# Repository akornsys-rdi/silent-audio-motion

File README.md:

# Silent audio motion

Silent audio motion, the system behind «Ver no es hablar» artwork

## Description

The device generates the movement of a magnet according to an input audio signal. For this purpose the device generates a PWM signal with polarity (positive and negative half cycle) to excite an electromagnet. This signal is proportional to an analog input signal (audio source). It has two symmetrical channels and it responds to different frequencies, signal levels and waveforms.

This repository includes all the necessary files of this project: The 3D files to be printed, the control board of the device and its firmware.

### Technical features

- Supply voltage: 12VDC
- Frequency range: 1KHz-0.1Hz (firmware capability)
- Input voltage: up to 3Vpp
- Input impedance: 20kΩ

### Status LED

The device includes an LED to show the state it is in, these states are:

- Permanent LED indicates that there is no signal on either channel, the output driver is off.
- Slow blinking LED (~8Hz) indicates clipping on output, input level needs to be lowered or ADJ trimmer needs to be adjusted if not calibrated.
- Fast flashing LED (~30Hz) indicates input level too high, input level needs to be lowered, input stage may be damaged.
- LED off in normal operation.

The status LED may take up to one second to respond to changes in the input.

## Testing the device

### Output driver test

Load the `test_outputs` program. It should generate signals on both output channels. The test firmware can generate different output patterns.
The test is successful when the solenoid connected to each channel moves at the frequency set in code, with the selected waveform.

### Input stage test

Load the 'test_inputs' program. The cursor of the trimmers must not be at the ends. This program must show per port the three inputs of each channel (use serial plotter). Connect an audio source with a signal below 10Hz to both channels.

The test is successful when:

- The values of the first and fourth signals should be the values of the inputs of the left and right audio channels respectively.
- The values of the second and fifth signals should be the values of the ADJ trimmers, and should be different from the ends.
- The values of the third and sixth signals are a comparison of the negative half-cycle with the TRG trimmers, and should show a square signal centered on the peaks of the audio inputs. If this square signal does not appear, move the TRG trimmers until it does.

One of the input signal half-cycles may be slightly smaller than the other.

## Calibrating the device

Set the 3Hz and 3Vpp sine wave signal to channel L, with the program 'test_inputs' loaded.

Adjust the ADJ trimmer immediately above the peak of the input signal, and below the STANDBY_THRESHOLD threshold (default 900). A good value is 817. Turning it counterclockwise increases the value, and turning it clockwise decreases it.

Change the frequency to 0.5Hz. Adjust the ADJ trimmer until it is as close to zero as possible. It should be shown only during negative half-cycles. Values too low show square signals during both half-cycles. Values too high are far from zero on negative half-cycles.
A good adjustment is to lower it until it is below zero and to go up until the trigger disappears in the positive semicircle, then add a quarter turn more. Turning clockwise lowers the value, turning counterclockwise raises it.

Repeat the process with the R channel.

Enter signal on both channels, the setting signals must overlap.

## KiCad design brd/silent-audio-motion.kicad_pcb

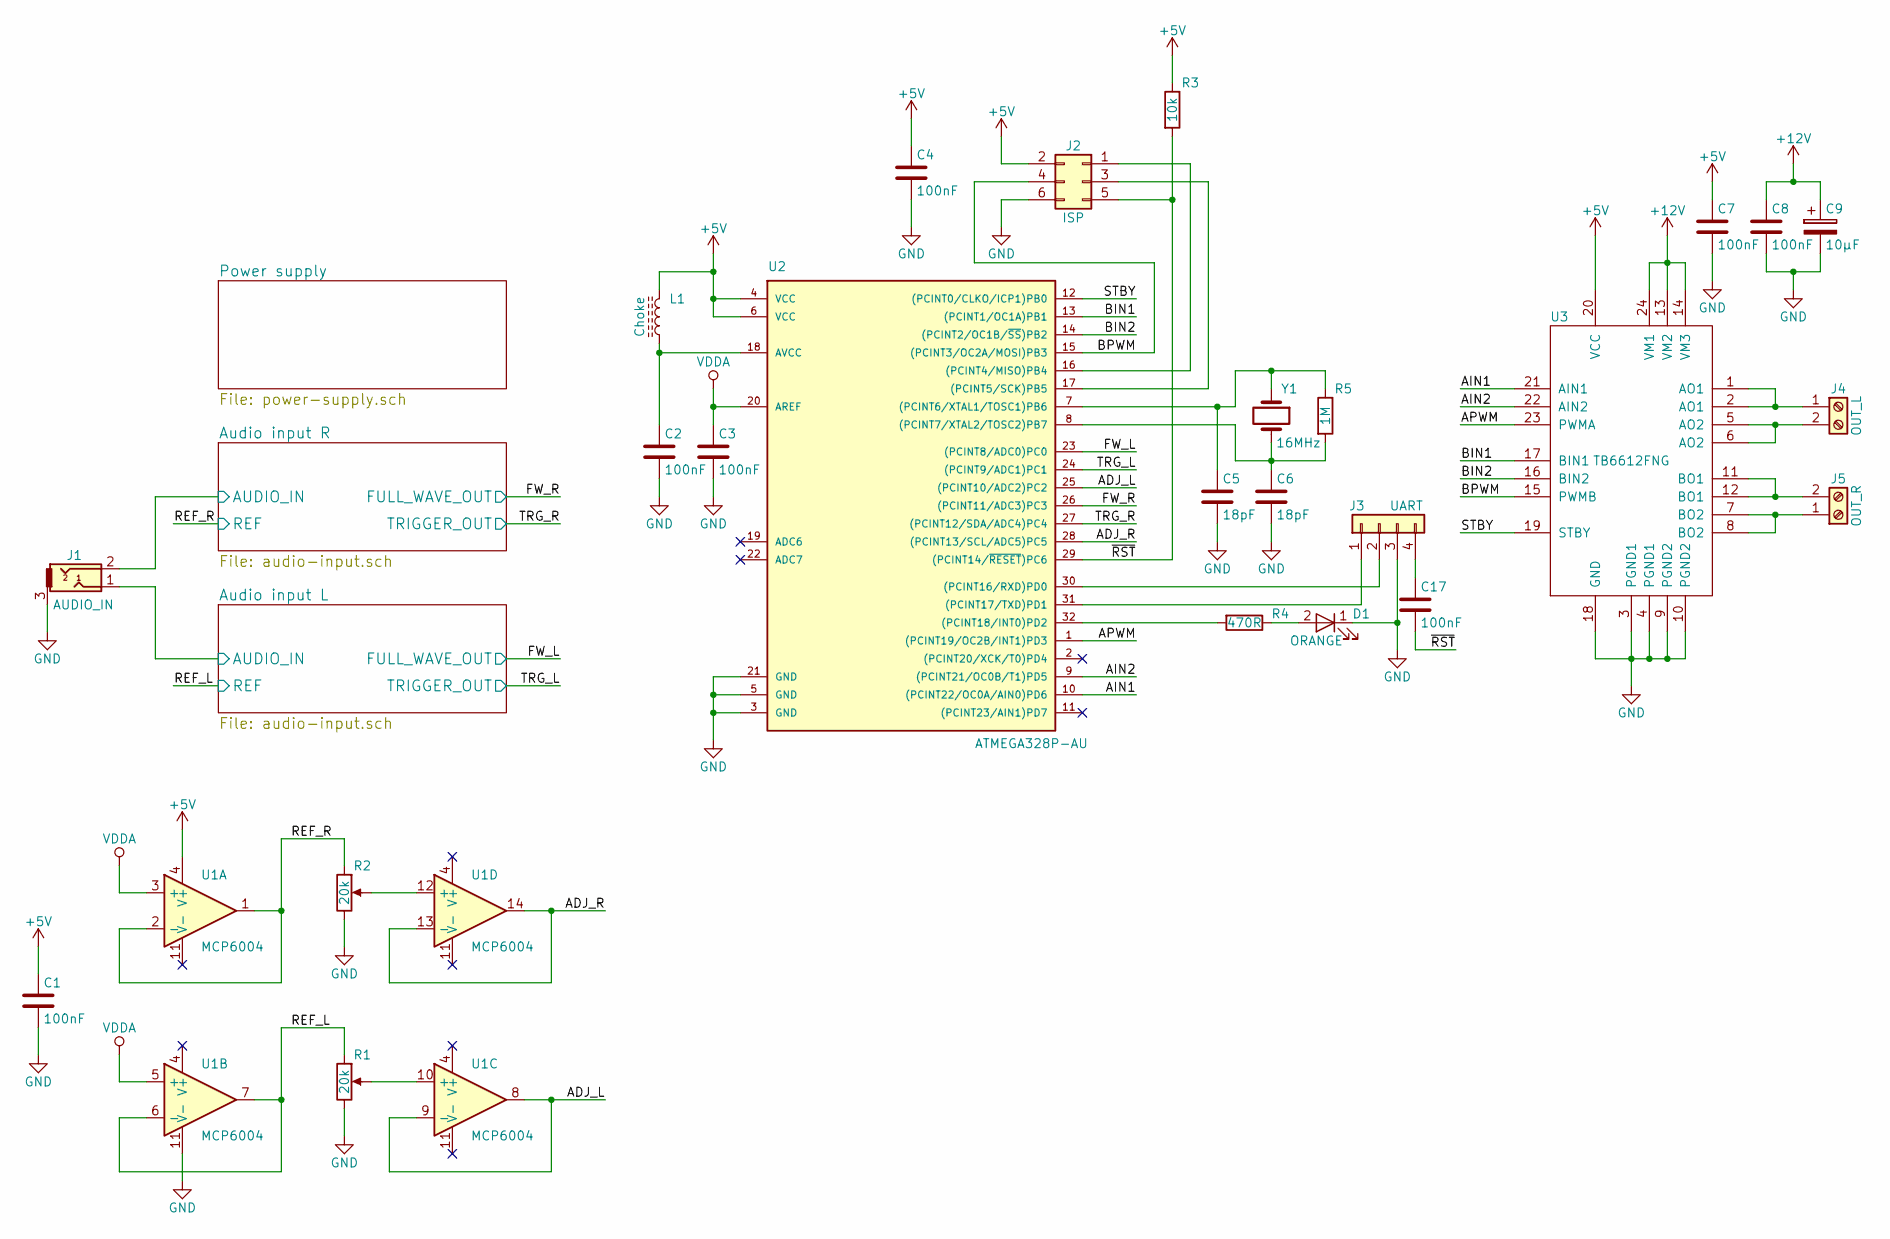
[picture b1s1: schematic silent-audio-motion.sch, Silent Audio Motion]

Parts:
C1, C2, C3, C4, C7, C8, C17: 100nF; C_0805; Manufacturer Part Number C0805C104J5RACTU
C5, C6: 18pF; C_0805; Manufacturer Part Number C0805C180J5GAC
C9: 10µF; CP_Elec_4x5.3; Manufacturer Part Number UWJ1C100MCL1GB
D1: ORANGE; LED_0805; Manufacturer Part Number LO R976-PS-1
J1: AUDIO_IN; STX-3200-3; Manufacturer Part Number STX-3200-3NB
J2: ISP; IDC-Header_2x03_Pitch2.54mm_Straight
J3: UART; Pin_Header_Straight_1x04_Pitch2.54mm
J4: OUT_L; TerminalBlock_Phoenix_MKDS1.5-2pol; Manufacturer Part Number 1888687
J5: OUT_R; TerminalBlock_Phoenix_MKDS1.5-2pol; Manufacturer Part Number 1888687
L1: Choke; L_0805_HandSoldering; Manufacturer Part Number BLM21PG331SN1D
R1, R2: 20k; Potentiometer_Trimmer_Bourns_3299P; Manufacturer Part Number 36KR20KLF
R3: 10k; R_0805_HandSoldering; Manufacturer Part Number CR0805-JW-103ELF
R4: 470R; R_0805_HandSoldering; Manufacturer Part Number CR0805-JW-471ELF
R5: 1M; R_0805_HandSoldering; Manufacturer Part Number CR0805-JW-105ELF
U1: MCP6004; TSSOP-14_4.4x5mm_Pitch0.65mm; Manufacturer Part Number MCP6004-I/ST
U2: ATMEGA328P-AU; TQFP-32_7x7mm_Pitch0.8mm; Manufacturer Part Number ATMEGA328P-AU
U3: TB6612FNG; SSOP-24_5.3x8.2mm_Pitch0.65mm; Manufacturer Part Number TB6612FNG,C,8,EL
Y1: 16MHz; Crystal_SMD_HC49-SD; Manufacturer Part Number ABLS-16.000MHZ-B4-T

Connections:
+5V: C1.1, C4.1, C7.1, J2.2, L1.2, R3.1, U1.4 (V+), U2.4 (VCC), U2.6 (VCC), U3.20 (VCC); also elsewhere on the board
+12V: C8.1, C9.1, U3.13 (VM2), U3.14 (VM3), U3.24 (VM1); also elsewhere on the board
/ADJ_L: U1.8, U1.9 (-), U2.25 ((PCINT10/ADC2)PC2)
/ADJ_R: U1.13 (-), U1.14, U2.28 ((PCINT13/SCL/ADC5)PC5)
/AIN1: U2.10 ((PCINT22/OC0A/AIN0)PD6), U3.21 (AIN1)
/AIN2: U2.9 ((PCINT21/OC0B/T1)PD5), U3.22 (AIN2)
/APWM: U2.1 ((PCINT19/OC2B/INT1)PD3), U3.23 (PWMA)
/Audio input L/AUDIO_IN: J1.1; also elsewhere on the board
/Audio input R/AUDIO_IN: J1.2; also elsewhere on the board
/BIN1: U2.13 ((PCINT1/OC1A)PB1), U3.17 (BIN1)
/BIN2: U2.14 ((PCINT2/OC1B/~SS~)PB2), U3.16 (BIN2)
/BPWM: J2.4, U2.15 ((PCINT3/OC2A/MOSI)PB3), U3.15 (PWMB)
/FW_L: U2.23 ((PCINT8/ADC0)PC0); also elsewhere on the board
/FW_R: U2.26 ((PCINT11/ADC3)PC3); also elsewhere on the board
/REF_L: R1.1, U1.6 (-), U1.7; also elsewhere on the board
/REF_R: R2.1, U1.1, U1.2 (-); also elsewhere on the board
/STBY: U2.12 ((PCINT0/CLKO/ICP1)PB0), U3.19 (STBY)
/TRG_L: U2.24 ((PCINT9/ADC1)PC1); also elsewhere on the board
/TRG_R: U2.27 ((PCINT12/SDA/ADC4)PC4); also elsewhere on the board
/~RST: C17.2, J2.5, R3.2, U2.29 ((PCINT14/~RESET~)PC6)
GND: C1.2, C2.2, C3.2, C4.2, C5.2, C6.2, C7.2, C8.2, C9.2, D1.1 (K), J1.3, J2.6, J3.3, R1.3, R2.3, U1.11 (V-), U2.3 (GND), U2.5 (GND), U2.21 (GND), U3.3 (PGND1), U3.4 (PGND1), U3.9 (PGND2), U3.10 (PGND2), U3.18 (GND); also elsewhere on the board
unnamed: C2.1, L1.1, U2.18 (AVCC)
unnamed: C5.1, R5.1, U2.7 ((PCINT6/XTAL1/TOSC1)PB6), Y1.1
unnamed: C6.1, R5.2, U2.8 ((PCINT7/XTAL2/TOSC2)PB7), Y1.2
unnamed: C17.1, J3.4
unnamed: D1.2 (A), R4.1
unnamed: J2.1, U2.16 ((PCINT4/MISO)PB4)
unnamed: J2.3, U2.17 ((PCINT5/SCK)PB5)
unnamed: J3.1, U2.31 ((PCINT17/TXD)PD1)
unnamed: J3.2, U2.30 ((PCINT16/RXD)PD0)
unnamed: J4.1, U3.1 (AO1), U3.2 (AO1)
unnamed: J4.2, U3.5 (AO2), U3.6 (AO2)
unnamed: J5.1, U3.7 (BO2), U3.8 (BO2)
unnamed: J5.2, U3.11 (BO1), U3.12 (BO1)
unnamed: R1.2, U1.10 (+)
unnamed: R2.2, U1.12 (+)
unnamed: R4.2, U2.32 ((PCINT18/INT0)PD2)
VDDA: C3.1, U1.3 (+), U1.5 (+), U2.20 (AREF); also elsewhere on the board

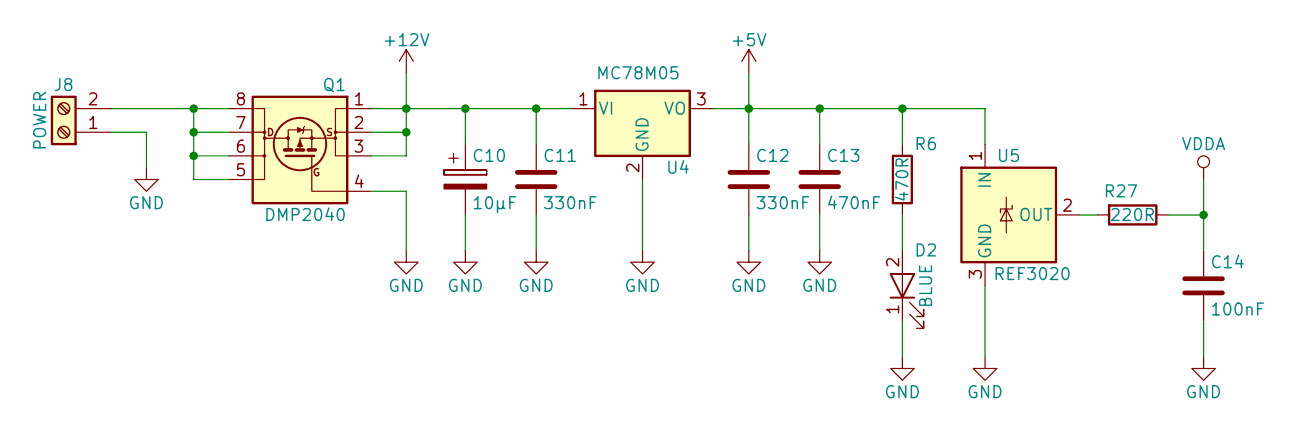
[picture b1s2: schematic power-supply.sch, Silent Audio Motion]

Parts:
C10: 10µF; CP_Elec_4x5.3; Manufacturer Part Number UWJ1C100MCL1GB
C11, C12: 330nF; C_0805; Manufacturer Part Number GMK212B7334KG-T
C13: 470nF; C_0805; Manufacturer Part Number TMK212BJ474KD-T
C14: 100nF; C_0805; Manufacturer Part Number C0805C104J5RACTU
D2: BLUE; LED_0805; Manufacturer Part Number APHCM2012QBC/D-F01
J8: POWER; TerminalBlock_Phoenix_MKDS1.5-2pol; Manufacturer Part Number 1888687
Q1: DMP2040; SOIC-8_3.9x4.9mm_Pitch1.27mm; Manufacturer Part Number DMP2040USS-13
R6: 470R; R_0805_HandSoldering; Manufacturer Part Number CR0805-JW-471ELF
R27: 220R; R_0805_HandSoldering; Manufacturer Part Number CR0805-JW-221ELF
U4: MC78M05; TO-252-2; Manufacturer Part Number MC78M05CDTRKG
U5: REF3020; SOT-23; Manufacturer Part Number REF3020AIDBZR

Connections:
+5V: C12.1, C13.1, R6.1, U4.3 (VO), U5.1 (IN); also elsewhere on the board
+12V: C10.1, C11.1, Q1.1 (S), Q1.2 (S), Q1.3 (S), U4.1 (VI); also elsewhere on the board
GND: C10.2, C11.2, C12.2, C13.2, C14.2, D2.1 (K), J8.1, Q1.4 (G), U4.2 (GND), U5.3 (GND); also elsewhere on the board
unnamed: D2.2 (A), R6.2
unnamed: J8.2, Q1.5 (D), Q1.6 (D), Q1.7 (D), Q1.8 (D)
unnamed: R27.2, U5.2 (OUT)
VDDA: C14.1, R27.1; also elsewhere on the board

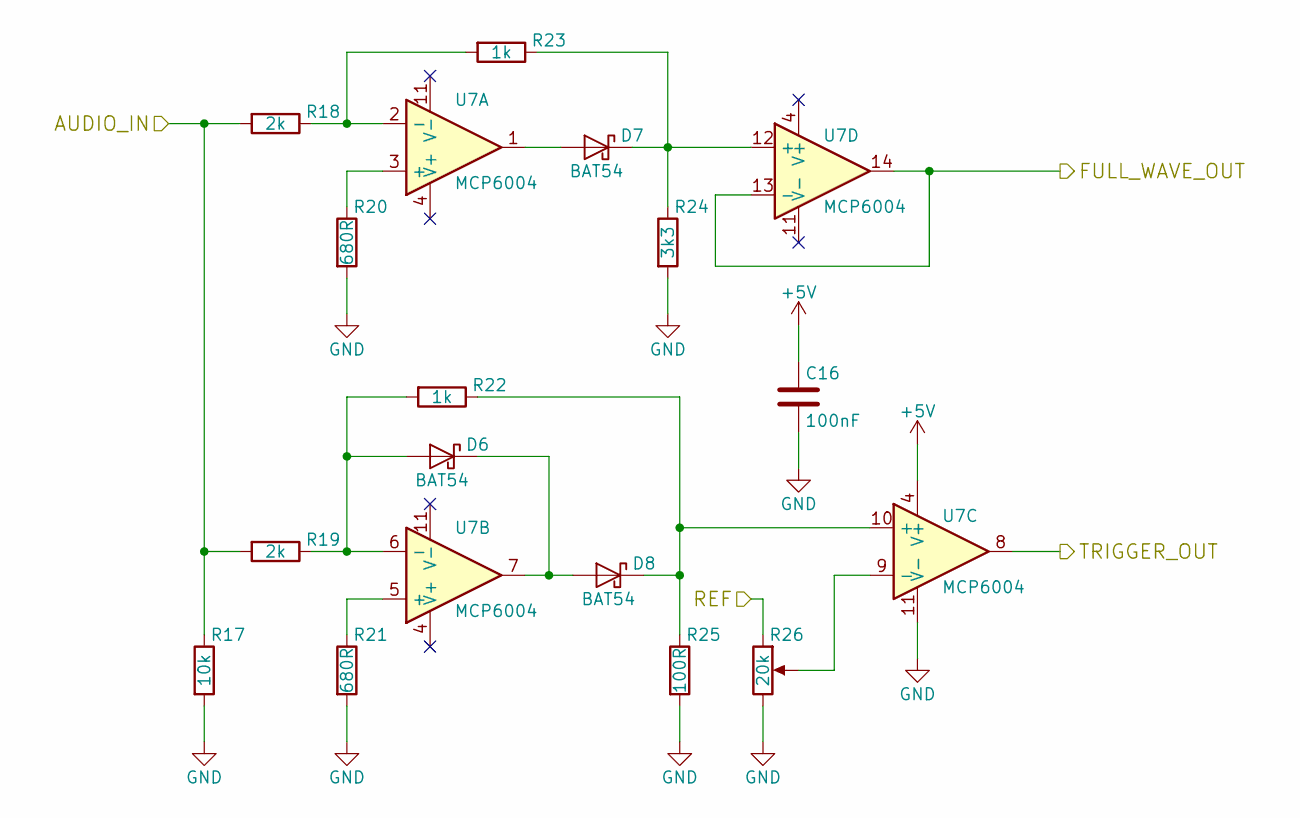
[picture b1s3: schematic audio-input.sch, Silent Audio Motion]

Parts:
C15: 100nF; C_0805; Manufacturer Part Number C0805C104J5RACTU
D3, D4, D5: BAT54; D_SOD-123; Manufacturer Part Number BAT54GWJ
R7: 10k; R_0805_HandSoldering; Manufacturer Part Number CR0805-JW-103ELF
R8, R9: 2k; R_0805_HandSoldering; Manufacturer Part Number CR0805-FX-2001ELF
R10, R11: 680R; R_0805_HandSoldering; Manufacturer Part Number CR0805-FX-6800ELF
R12, R13: 1k; R_0805_HandSoldering; Manufacturer Part Number CR0805-FX-1001ELF
R14: 3k3; R_0805_HandSoldering; Manufacturer Part Number CR0805-FX-3301ELF
R15: 100R; R_0805_HandSoldering; Manufacturer Part Number CR0805-FX-1000ELF
R16: 20k; Potentiometer_Trimmer_Bourns_3299P; Manufacturer Part Number 36KR20KLF
U6: MCP6004; TSSOP-14_4.4x5mm_Pitch0.65mm; Manufacturer Part Number MCP6004-I/ST

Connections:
+5V: C15.1, U6.4 (V+); also elsewhere on the board
/Audio input L/AUDIO_IN: R7.1, R8.2, R9.2; also elsewhere on the board
/FW_L: U6.13 (-), U6.14; also elsewhere on the board
/REF_L: R16.1; also elsewhere on the board
/TRG_L: U6.8; also elsewhere on the board
GND: C15.2, R7.2, R10.2, R11.2, R14.2, R15.2, R16.3, U6.11 (V-); also elsewhere on the board
unnamed: D3.1 (K), D5.2 (A), U6.7
unnamed: D3.2 (A), R9.1, R12.2, U6.6 (-)
unnamed: D4.1 (K), R13.1, R14.1, U6.12 (+)
unnamed: D4.2 (A), U6.1
unnamed: D5.1 (K), R12.1, R15.1, U6.10 (+)
unnamed: R10.1, U6.3 (+)
unnamed: R11.1, U6.5 (+)
unnamed: R8.1, R13.2, U6.2 (-)
unnamed: R16.2, U6.9 (-)

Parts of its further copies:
C16: 100nF; C_0805; Manufacturer Part Number C0805C104J5RACTU
D6, D7, D8: BAT54; D_SOD-123; Manufacturer Part Number BAT54GWJ
R17: 10k; R_0805_HandSoldering; Manufacturer Part Number CR0805-JW-103ELF
R18, R19: 2k; R_0805_HandSoldering; Manufacturer Part Number CR0805-FX-2001ELF
R20, R21: 680R; R_0805_HandSoldering; Manufacturer Part Number CR0805-FX-6800ELF
R22, R23: 1k; R_0805_HandSoldering; Manufacturer Part Number CR0805-FX-1001ELF
R24: 3k3; R_0805_HandSoldering; Manufacturer Part Number CR0805-FX-3301ELF
R25: 100R; R_0805_HandSoldering; Manufacturer Part Number CR0805-FX-1000ELF
R26: 20k; Potentiometer_Trimmer_Bourns_3299P; Manufacturer Part Number 36KR20KLF
U7: MCP6004; TSSOP-14_4.4x5mm_Pitch0.65mm; Manufacturer Part Number MCP6004-I/ST

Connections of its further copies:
+5V: C16.1, U7.4 (V+); also elsewhere on the board
/Audio input R/AUDIO_IN: R17.1, R18.2, R19.2; also elsewhere on the board
/FW_R: U7.13 (-), U7.14; also elsewhere on the board
/REF_R: R26.1; also elsewhere on the board
/TRG_R: U7.8; also elsewhere on the board
GND: C16.2, R17.2, R20.2, R21.2, R24.2, R25.2, R26.3, U7.11 (V-); also elsewhere on the board
unnamed: D6.1 (K), D8.2 (A), U7.7
unnamed: D6.2 (A), R19.1, R22.2, U7.6 (-)
unnamed: D7.1 (K), R23.1, R24.1, U7.12 (+)
unnamed: D7.2 (A), U7.1
unnamed: D8.1 (K), R22.1, R25.1, U7.10 (+)
unnamed: R18.1, R23.2, U7.2 (-)
unnamed: R20.1, U7.3 (+)
unnamed: R21.1, U7.5 (+)
unnamed: R26.2, U7.9 (-)

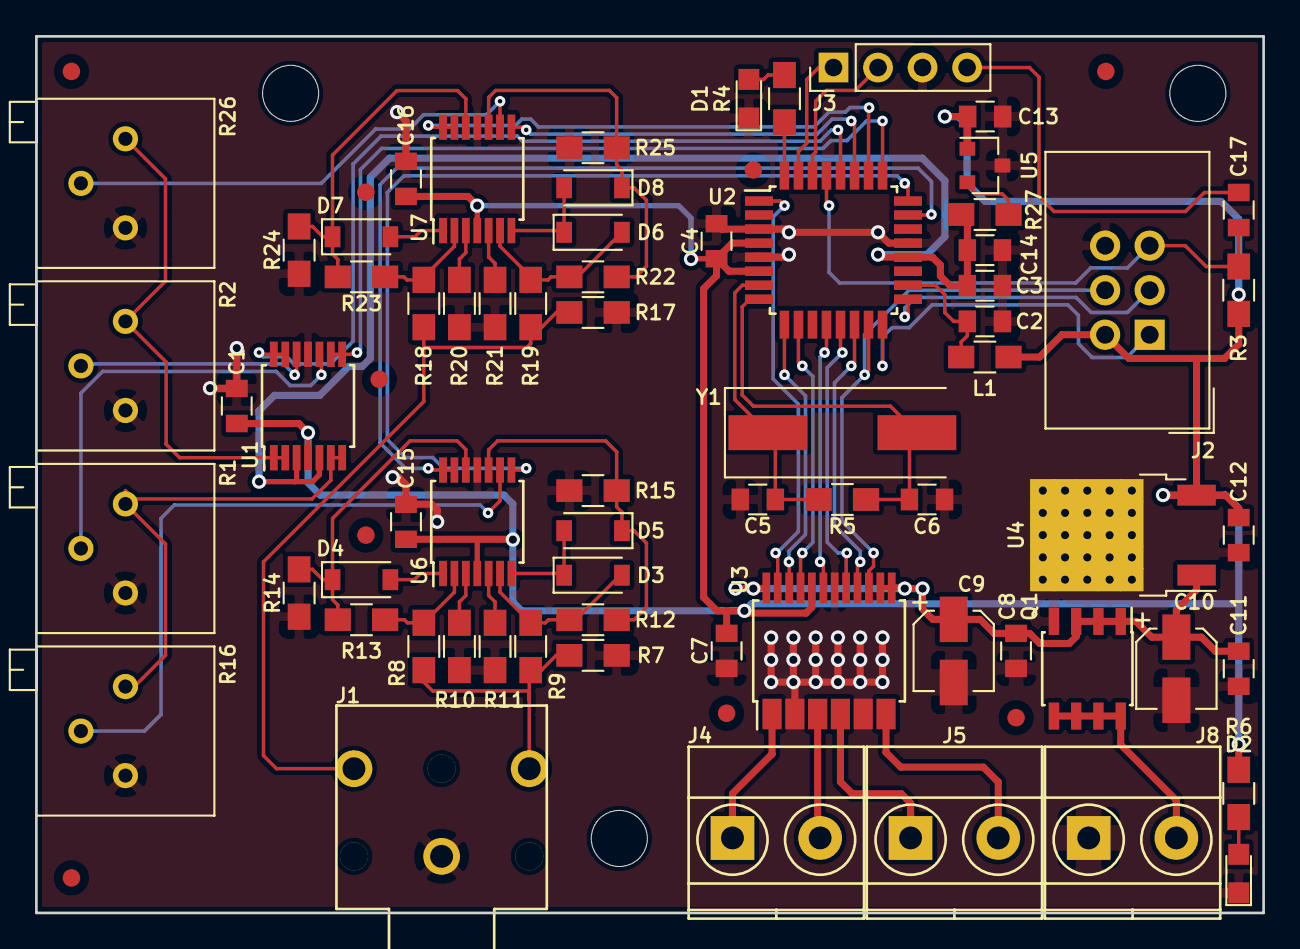
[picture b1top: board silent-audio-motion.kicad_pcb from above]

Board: 2 copper layers, 70.0 x 50.0 mm, 68 parts (0 on the bottom side), 59 nets.

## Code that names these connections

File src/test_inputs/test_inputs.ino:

#define STBY        8
#define APWM        3
#define AIN1        6
#define AIN2        5
#define BPWM        11
#define BIN1        9
#define BIN2        10
#define FW_L        A0
#define TRG_L       A1
#define ADJ_L       A2
#define FW_R        A3
#define TRG_R       A4
#define ADJ_R       A5
#define DEBUG       2

void setup() {
    analogReference(EXTERNAL);
    pinMode(DEBUG, OUTPUT);
    pinMode(TRG_L, INPUT);
    pinMode(TRG_R, INPUT);
    ADCSRA = ADCSRA & B11111000 | B00000100;
    Serial.begin(115200);
}

void loop() {
    Serial.print(analogRead(FW_L));
    Serial.print(" ");
    Serial.print(analogRead(ADJ_L));
    Serial.print(" ");
    if (digitalRead(TRG_L)) Serial.print(1023);
    else Serial.print(0);
    Serial.print(" ");
    Serial.print(analogRead(FW_R));
    Serial.print(" ");
    Serial.print(analogRead(ADJ_R));
    Serial.print(" ");
    if (digitalRead(TRG_R)) Serial.println(1023);
    else Serial.println(0);
    digitalWrite(DEBUG, !digitalRead(DEBUG));
    delay(5);
}

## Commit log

2019-11-03 añadido application note de rectificadores
2019-11-03 añadido diseño de pcb
2020-02-25 subido código paramétrico con test
2020-02-25 subido diseño 3d
2020-07-28 actualizado diseño 3d
2020-07-28 añadidos codigos de prueba y calibracion
2020-07-28 corregido problema con referencia analogica
2020-07-28 añadido pin DTR para reset en cabecera UART
2020-07-28 subido nuevo firmware de control
2020-07-28 actualizado cajetin de datos
2020-07-28 generado esquematico PDF
2020-07-28 generado PDF de PCB
2020-07-28 regenerados gerbers
2020-07-28 actualizado README con documentación del proyecto
2020-07-29 eliminados parrafos duplicados
2020-08-19 añadido datasheet de potenciometro pv36
2020-08-19 actualizado 3d con componentes de la pcb

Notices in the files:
brd/silent-audio-motion.kicad_pcb:
Copyright © 2019 kwendenarmo
Released under GNU/GPL 3 License
https://www.gnu.org/licenses/gpl.html
